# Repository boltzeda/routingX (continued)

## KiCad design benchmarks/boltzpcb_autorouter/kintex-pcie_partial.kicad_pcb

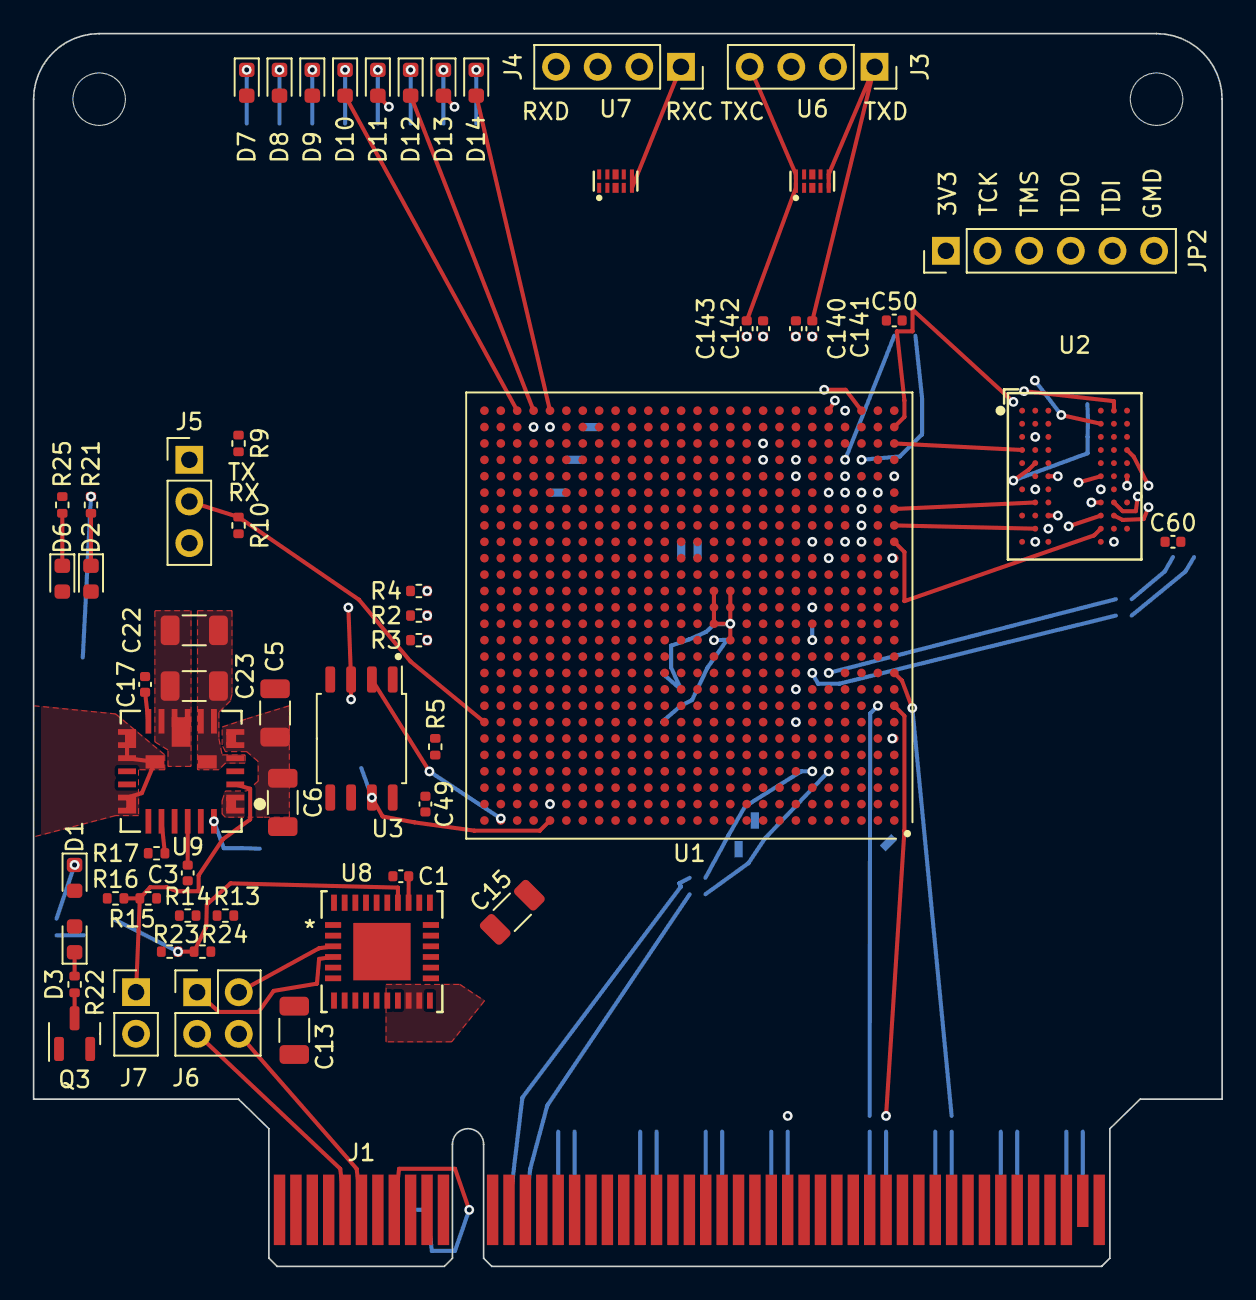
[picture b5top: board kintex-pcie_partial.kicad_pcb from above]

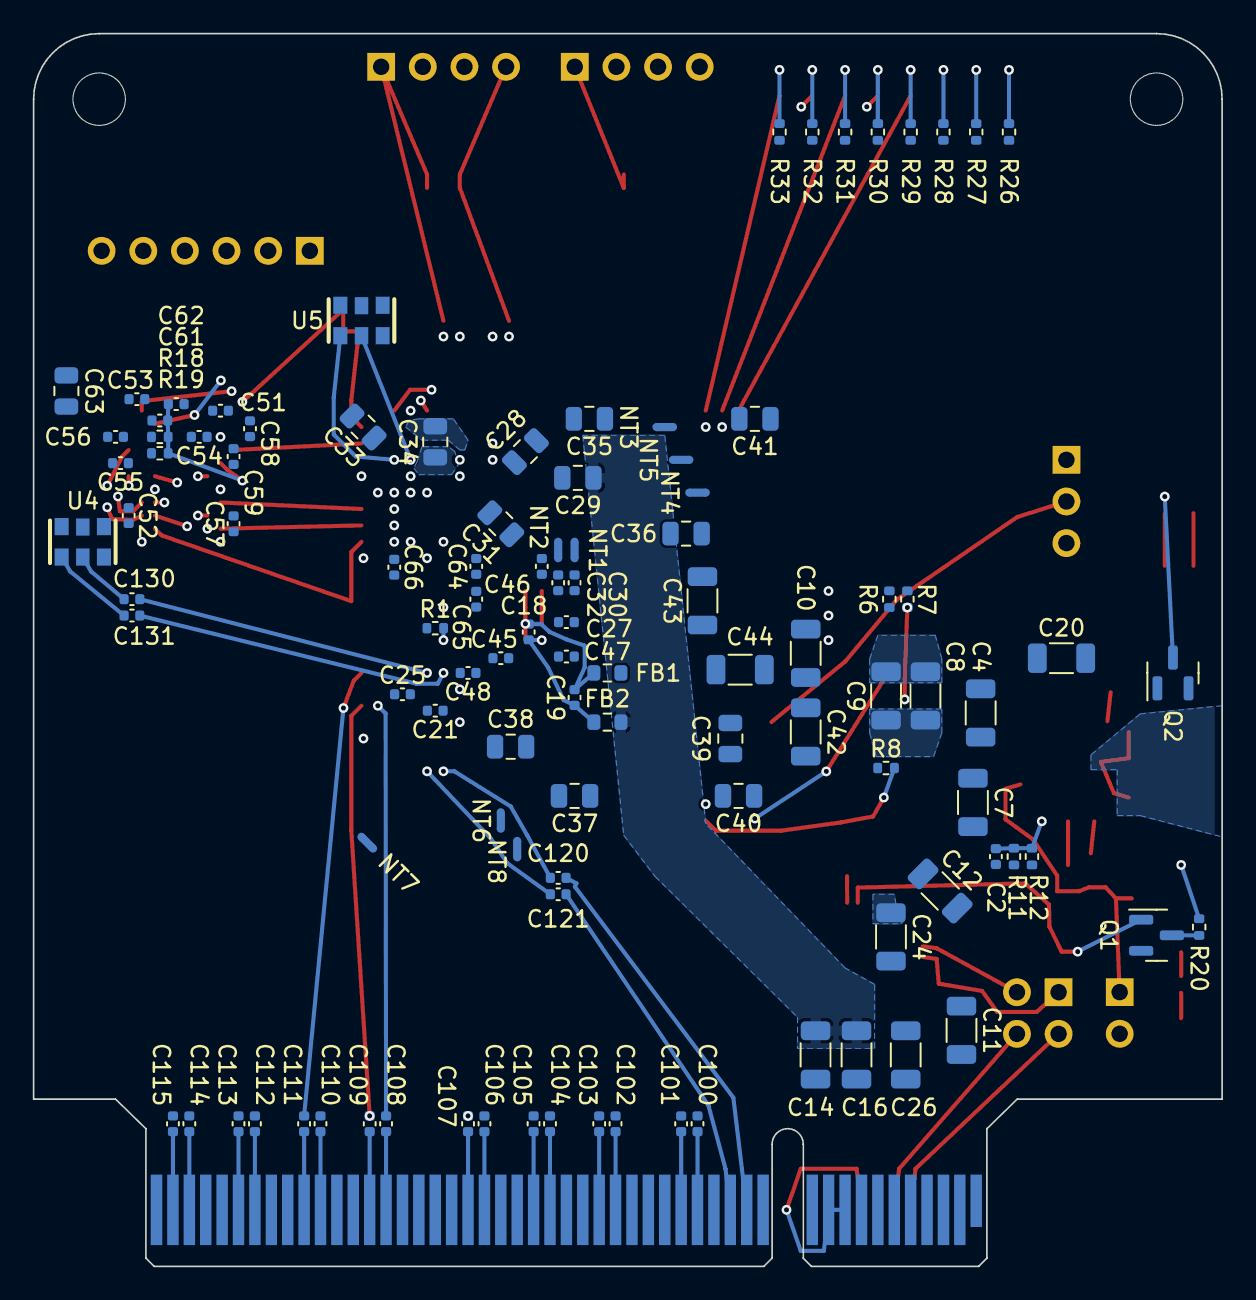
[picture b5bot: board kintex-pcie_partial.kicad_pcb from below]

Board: 8 copper layers, 72.5 x 75.2 mm, 166 parts (105 on the bottom side), 178 nets.

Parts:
C1, C17, C19: 1uF; C_0402_1005Metric
C2, C3: 4.7nF; C_0402_1005Metric
C4, C5, C6, C7, C8, C9, C10, C11, C12, C13, C14, C15, C16, C20, C22, C23, C24, C26: 22uF; C_1206_3216Metric
C18, C49, C50, C51, C52, C53, C54, C55, C56, C57, C58, C59, C60, C61, C62, C100, C101, C102, C103, C104, C105, C106, C107, C108, C109, C110, C111, C112, C113, C114, C115, C120, C121, C130, C131, C140, C141, C142, C143: 100nF; C_0402_1005Metric
C21, C25, C27, C30, C32, C45, C46, C47, C48, C64, C65, C66: 4.7uF; C_0402_1005Metric
C28, C29, C31, C33, C34, C35, C36, C37, C38, C39, C40, C41, C63: 47uF; C_0805_2012Metric
C42, C43, C44: 100uF; C_1206_3216Metric
D1, D2, D3, D6: GLED; LED_0603_1608Metric
D7, D8, D9, D10, D11, D12, D13, D14: RLED; LED_0603_1608Metric
FB1, FB2: 600R@100MHz; R_0603_1608Metric
H1, H2: MountingHole; MountingHole_3.2mm_M3
J1: Bus_PCI_Express_x8; BUS_PCIexpress_x8
J3: B2B_TX; PinSocket_1x04_P2.54mm_Vertical
J4: B2B_RX; PinSocket_1x04_P2.54mm_Vertical
J5: UART; PinHeader_1x03_P2.54mm_Vertical
J6: I2C_LINK; PinHeader_2x02_P2.54mm_Vertical
J7: 1V_EN; PinHeader_1x02_P2.54mm_Vertical
JP2: JTAG; PinHeader_1x06_P2.54mm_Vertical
NT1, NT2, NT3, NT4, NT5, NT6, NT7, NT8: NetTie_2; NetTie-2_SMD_Pad0.5mm
Q1, Q2, Q3: BSS138; SOT-23
R1: 100R; R_0402_1005Metric
R2, R3, R4, R5, R6, R7, R8, R9, R10, R20, R21, R22, R25, R26, R27, R28, R29, R30, R31, R32, R33: 4K7; R_0402_1005Metric
R11, R18, R19: 2K; R_0402_1005Metric
R12, R14, R16, R24: 3K; R_0402_1005Metric
R13, R15, R17, R23: 15K; R_0402_1005Metric
U1: XC7K160T-FFG676; Xilinx_FFG676
U2: MT47H64M8SH; FBGA-60_L10.0-W8.0-P0.80-TL_MICRON_MT47H64M8SH
U3: W25Q128JVS; SOIC-8_5.23x5.23mm_P1.27mm
U4, U5: OB3225125MLDB6SI-00; OSC-SMD_6P-L3.2-W2.5-BL_SG3225EAN
U6, U7: TPD4E02B04DQAR; USON-10_L2.5-W1.0-P0.50-BL
U8: MPM54304GMN-0000; LGA7x7x2_MNP
U9: MPM3683GQN-7-P; MPM3683GQN-7

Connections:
+1V0: C4.1, C5.1, C6.1, C7.1, C8.1, C9.1, C10.1, C27.1, C30.1, C32.1, C42.1, C43.1, C44.1, C45.1, C46.1, C47.1, C48.1, NT2.2, U1.J9 (VCCINT), U1.K8 (VCCINT), U1.K10 (VCCINT), U1.K12 (VCCINT), U1.K14 (VCCINT), U1.L9 (VCCINT), U1.L13 (VCCINT), U1.L15 (VCCINT), U1.M8 (VCCINT), U1.M14 (VCCINT), U1.N9 (VCCINT), U1.N13 (VCCBRAM), U1.N15 (VCCINT), U1.P14 (VCCINT), U1.R13 (VCCBRAM), U1.R15 (VCCINT), U1.T12 (VCCBRAM), U1.T14 (VCCINT), U1.U13 (VCCBRAM), U1.U15 (VCCINT), U9.1 (VOUT), U9.6 (VOUT)
+1V8: C14.1, C16.1, C28.1, C29.1, C31.1, C33.1, C34.1, C35.1, C50.1, C51.1, C52.1, C53.1, C54.1, C55.1, C56.1, C57.1, C58.1, C59.1, C60.1, C62.2, C63.1, C64.1, C65.1, C66.1, FB2.2, NT3.2, R18.1, U1.AA1 (VCCO_34), U1.AA11 (VCCO_33), U1.AB8 (VCCO_33), U1.AB18 (VCCO_32), U1.AC5 (VCCO_34), U1.AC15 (VCCO_32), U1.AD2 (VCCO_34), U1.AD12 (VCCO_33), U1.AE9 (VCCO_33), U1.AE19 (VCCO_32), U1.AF6 (VCCO_34), U1.AF16 (VCCO_32), U1.L11 (VCCAUX), U1.M10 (VCCAUX), U1.N6 (MGTVCCAUX), U1.P8 (VCCAUX_IO_G0), U1.P10 (VCCAUX), U1.R9 (VCCAUX_IO_G0), U1.T8 (VCCAUX_IO_G0), U1.T10 (VCCAUX), U1.U3 (VCCO_34), U1.U11 (VCCAUX), U1.V10 (VCCO_33), U1.W7 (VCCO_33), U1.W17 (VCCO_32), U1.Y4 (VCCO_34), U1.Y14 (VCCO_32), U2.A1 (VDD), U2.A9 (VDDQ), U2.C1 (VDDQ), U2.C3 (VDDQ), U2.C7 (VDDQ), U2.C9 (VDDQ), U2.E1 (VDDL), U2.E9 (VDD), U2.H9 (VDD), U2.L1 (VDD), U4.1 (OE), U4.6 (VDD), U5.1 (OE), U5.6 (VDD), U8.14 (VOUT1), U8.15 (VOUT1)
+3V3: C11.1, C13.1, C36.1, C37.1, C38.1, C39.1, C40.1, C41.1, C49.1, JP2.1, NT4.2, R2.2, R3.2, R4.2, R5.1, R6.1, R7.1, R8.1, R9.1, R10.1, U1.A11 (VCCO_16), U1.A21 (VCCO_14), U1.AA21 (VCCO_12), U1.AC25 (VCCO_12), U1.AD22 (VCCO_12), U1.AF26 (VCCO_12), U1.B8 (VCCO_16), U1.B18 (VCCO_15), U1.C15 (VCCO_16), U1.C25 (VCCO_14), U1.D12 (VCCO_16), U1.D22 (VCCO_14), U1.E9 (VCCO_16), U1.E19 (VCCO_15), U1.F16 (VCCO_15), U1.F26 (VCCO_14), U1.G13 (VCCO_16), U1.G23 (VCCO_14), U1.H10 (VCCO_16), U1.H20 (VCCO_15), U1.J17 (VCCO_15), U1.K24 (VCCO_13), U1.L7 (VCCO_0), U1.L21 (VCCO_14), U1.M18 (VCCO_15), U1.N25 (VCCO_13), U1.P7 (CFGBVS_0), U1.P22 (VCCO_13), U1.R19 (VCCO_13), U1.T5 (M0_0), U1.T6 (VCCO_0), U1.T16 (VCCO_13), U1.T26 (VCCO_13), U1.U23 (VCCO_12), U1.V20 (VCCO_12), U1.Y24 (VCCO_12), U3.8 (VCC), U8.8 (VOUT2), U8.9 (VOUT2)
+12V: C20.1, C22.1, C23.1, C24.1, C26.1, D1.2 (A), D2.2 (A), D3.2 (A), D6.2 (A), J1.A2 (+12V), J1.A3 (+12V), J1.B1 (+12V), J1.B2 (+12V), J1.B3 (+12V), R13.2, R15.2, R23.2, U8.28 (VIN), U8.29 (VIN), U9.5 (VIN), U9.8 (VIN), U9.9 (VIN), U9.27 (VIN)
/1V_EN: J7.1, R15.1, R16.2, U9.3 (EN)
/1V_PG: Q2.1 (G), R13.1, R14.2, U8.19 (EN), U9.4 (PG)
/3V3 PCIE: J1.A9 (+3.3V), J1.A10 (+3.3V), J1.B8 (+3.3V)
/B2B_RXC_N: J4.1, U1.AC11 (IO_L13N_T2_MRCC_33), U7.5 (IO4), U7.6 (NC)
/B2B_RXC_P: J4.2, U1.AB11 (IO_L13P_T2_MRCC_33), U7.4 (IO3), U7.7 (NC)
/B2B_RXD_N: J4.3, U1.AD13 (IO_L17N_T2_33), U7.2 (IO2), U7.9 (NC)
/B2B_RXD_P: J4.4, U1.AC13 (IO_L17P_T2_33), U7.1 (IO1), U7.10 (NC)
/B2B_TXC_C_N: C142.1, U1.AD9 (IO_L12N_T1_MRCC_33)
/B2B_TXC_C_P: C143.1, U1.AC9 (IO_L12P_T1_MRCC_33)
/B2B_TXC_N: C142.2, J3.3, U6.2 (IO2), U6.9 (NC)
/B2B_TXC_P: C143.2, J3.4, U6.1 (IO1), U6.10 (NC)
/B2B_TXD_C_N: C141.1, U1.AC7 (IO_L10N_T1_33)
/B2B_TXD_C_P: C140.1, U1.AB7 (IO_L10P_T1_33)
/B2B_TXD_N: C141.2, J3.1, U6.5 (IO4), U6.6 (NC)
/B2B_TXD_P: C140.2, J3.2, U6.4 (IO3), U6.7 (NC)
/DDR_125_N: U1.AC3 (IO_L14N_T2_SRCC_34), U5.4 (OUT+)
/DDR_125_P: U1.AC4 (IO_L14P_T2_SRCC_34), U5.5 (OUT-)
/DONE: R2.1, U1.J7 (DONE_0)
/FB: C2.2, R11.2, R12.1, U9.26 (VO_SENSE_P)
/GTX_125_C_N: C130.1, U4.5 (OUT-)
/GTX_125_C_P: C131.1, U4.4 (OUT+)
/GTX_125_N: C130.2, U1.K5 (MGTREFCLK1N_115)
/GTX_125_P: C131.2, U1.K6 (MGTREFCLK1P_115)
/INIT: R3.1, U1.G7 (INIT_B_0)
/LED0: D7.2 (A), U1.AE25 (IO_L23N_T3_12)
/LED1: D8.2 (A), U1.AF25 (IO_L20N_T3_12)
/LED2: D9.2 (A), U1.AD24 (IO_L16N_T2_12)
/LED3: D10.2 (A), U1.AF24 (IO_L20P_T3_12)
/LED4: D11.2 (A), U1.AE23 (IO_L22P_T3_12)
/LED5: D12.2 (A), U1.AF23 (IO_L22N_T3_12)
/LED6: D13.2 (A), U1.AE22 (IO_L24P_T3_12)
/LED7: D14.2 (A), U1.AF22 (IO_L24N_T3_12)
/MGTAVCC: C12.1, C21.1, NT6.2, U1.C6 (MGTAVCC), U1.E6 (MGTAVCC), U1.G6 (MGTAVCC), U1.J6 (MGTAVCC), U1.L6 (MGTAVCC), U8.1 (VOUT3), U8.32 (VOUT3)
/MGTAVTT: C15.1, C25.1, NT7.2, R1.1, U1.B3 (MGTAVTT), U1.C2 (MGTAVTT), U1.D3 (MGTAVTT), U1.G2 (MGTAVTT), U1.H3 (MGTAVTT), U1.L2 (MGTAVTT), U1.M3 (MGTAVTT), U1.M5 (MGTAVTTRCAL_115), U8.22 (VOUT4), U8.23 (VOUT4)
/MPM_PG: Q1.1 (G), R23.1, R24.2, U8.26 (GPIO)
/MPM_SCK: J6.1, U8.4 (SCL)
/MPM_SDA: J6.2, U8.3 (SDA)
/PCIE_SCK: J1.B5 (SMCLK), J6.3
/PCIE_SDA: J1.B6 (SMDAT), J6.4
/PCIE_TX0_C_N: C101.1, J1.A17 (PERn0)
/PCIE_TX0_C_P: C100.1, J1.A16 (PERp0)
/PCIE_TX1_C_N: C103.1, J1.A22 (PERn1)
/PCIE_TX1_C_P: C102.1, J1.A21 (PERp1)
/PCIE_TX2_C_N: C105.1, J1.A26 (PERn2)
/PCIE_TX2_C_P: C104.1, J1.A25 (PERp2)
/PCIE_TX3_C_N: C107.1, J1.A30 (PERn3)
/PCIE_TX3_C_P: C106.1, J1.A29 (PERp3)
/PCIE_TX4_C_N: C109.1, J1.A36 (PERn4)
/PCIE_TX4_C_P: C108.1, J1.A35 (PERp4)
/PCIE_TX5_C_N: C111.1, J1.A40 (PERn5)
/PCIE_TX5_C_P: C110.1, J1.A39 (PERp5)
/PCIE_TX6_C_N: C113.1, J1.A44 (PERn6)
/PCIE_TX6_C_P: C112.1, J1.A43 (PERp6)
/PCIE_TX7_C_N: C115.1, J1.A48 (PERn7)
/PCIE_TX7_C_P: C114.1, J1.A47 (PERp7)
/PERST: J1.A11 (~PERST), J7.2, Q3.1 (G)
/PROGRAM: R4.1, U1.P6 (PROGRAM_B_0)
/REFCLK_C_N: C121.2, J1.A14 (REFCLK-)
/REFCLK_C_P: C120.2, J1.A13 (REFCLK+)
/SPI_CLK: U1.C8 (CCLK_0), U3.6 (CLK)
/SPI_CS: R6.2, U1.C23 (IO_L6P_T0_FCS_B_14), U3.1 (~CS)
/SPI_D0: U1.B24 (IO_L1P_T0_D00_MOSI_14), U3.5 (DI(IO0))
/SPI_D1: U1.A25 (IO_L1N_T0_D01_DIN_14), U3.2 (DO(IO1))
/SPI_D2: R7.2, U1.B22 (IO_L2P_T0_D02_14), U3.3 (IO2)
/SPI_D3: R8.2, U1.A22 (IO_L2N_T0_D03_14), U3.7 (IO3)
/SW: U9.14 (SW), U9.16 (SW), U9.19 (SW), U9.28 (SW)
/TCK: JP2.2, U1.L8 (TCK_0)
/TDI: JP2.5, U1.R6 (TDI_0)
/TDO: JP2.4, U1.R7 (TDO_0)
/TMS: JP2.3, U1.N8 (TMS_0)
/UART_RX: J5.2, R10.2, U1.G26 (IO_L16N_T2_A15_D31_14)
/UART_TX: J5.1, R9.2, U1.H26 (IO_L18N_T2_A11_D27_14)
/VSENSE_N: NT1.2, R12.2, U9.25 (VO_SENSE_N)
/VSENSE_P: C2.1, NT2.1, R11.1
DDR_A0: U1.AA5 (IO_L15P_T2_DQS_34), U2.H8 (A0)
DDR_A1: U1.AC2 (IO_L11N_T1_SRCC_34), U2.H3 (A1)
DDR_A2: U1.W3 (IO_L4N_T0_34), U2.H7 (A2)
DDR_A3: U1.Y2 (IO_L7N_T1_34), U2.J2 (A3)
DDR_A4: U1.V4 (IO_L6P_T0_34), U2.J8 (A4)
DDR_A5: U1.AA3 (IO_L12P_T1_MRCC_34), U2.J3 (A5)
DDR_A6: U1.V6 (IO_L5N_T0_34), U2.J7 (A6)
DDR_A7: U1.W1 (IO_L10P_T1_34), U2.K2 (A7)
DDR_A8: U1.V2 (IO_L8P_T1_34), U2.K8 (A8)
DDR_A9: U1.Y3 (IO_L7P_T1_34), U2.K3 (A9)
DDR_A10: U1.Y1 (IO_L10N_T1_34), U2.H2 (A10)
DDR_A11: U1.V1 (IO_L8N_T1_34), U2.K7 (A11)
DDR_A12: U1.V3 (IO_L4P_T0_34), U2.L2 (A12)
DDR_A13: U1.U5 (IO_L1N_T0_34), U2.L8 (A13)
DDR_BA0: U1.AA2 (IO_L12N_T1_MRCC_34), U2.G2 (BA0)
DDR_BA1: U1.AC1 (IO_L9N_T1_DQS_34), U2.G3 (BA1)
DDR_CAS: U1.AA4 (IO_L13P_T2_MRCC_34), U2.G7 (~CAS)
DDR_CKE: U1.AB2 (IO_L11P_T1_SRCC_34), U2.F2 (CKE)
DDR_CK_N: U1.W5 (IO_L3N_T0_DQS_34), U2.F8 (~CK)
DDR_CK_P: U1.W6 (IO_L3P_T0_DQS_34), U2.E8 (CK)
DDR_DM: U1.AE3 (IO_L22P_T3_34), U2.B3 (DM)
DDR_DQ0: U1.AE5 (IO_L23N_T3_34), U2.C8 (DQ0)
DDR_DQ1: U1.AE1 (IO_L20N_T3_34), U2.C2 (DQ1)
DDR_DQ2: U1.AD3 (IO_L19N_T3_VREF_34), U2.D7 (DQ2)
DDR_DQ3: U1.AD4 (IO_L19P_T3_34), U2.D3 (DQ3)
DDR_DQ4: U1.AD1 (IO_L20P_T3_34), U2.D1 (DQ4)
DDR_DQ5: U1.AF3 (IO_L24P_T3_34), U2.D9 (DQ5)
DDR_DQ6: U1.AE2 (IO_L22N_T3_34), U2.B1 (DQ6)
DDR_DQ7: U1.AE6 (IO_L23P_T3_34), U2.B9 (DQ7)
DDR_DQS_N: U1.AF4 (IO_L21N_T3_DQS_34), U2.A8 (~DQS/NU)
DDR_DQS_P: U1.AF5 (IO_L21P_T3_DQS_34), U2.B7 (DQS)
DDR_ODT: U1.AB4 (IO_L13N_T2_MRCC_34), U2.F9 (ODT)
DDR_RAS: U1.U1 (IO_L2N_T0_34), U2.F7 (~RAS)
DDR_WE: U1.AB1 (IO_L9P_T1_DQS_34), U2.F3 (~WE)
GND: C1.2, C3.1, C4.2, C5.2, C6.2, C7.2, C8.2, C9.2, C10.2, C11.2, C12.2, C13.2, C14.2, C15.2, C16.2, C17.2, C20.2, C21.2, C22.2, C23.2, C24.2, C25.2, C26.2, C27.2, C28.2, C29.2, C30.2, C31.2, C32.2, C33.2, C34.2, C35.2, C36.2, C37.2, C38.2, C39.2, C40.2, C41.2, C42.2, C43.2, C44.2, C45.2, C46.2, C47.2, C48.2, C49.2, C50.2, C51.2, C52.2, C53.2, C54.2, C55.2, C56.2, C57.2, C58.2, C59.2, C60.2, C61.2, C63.2, C64.2, C65.2, C66.2, FB1.2, J1.A4 (GND), J1.A12 (GND), J1.A15 (GND), J1.A18 (GND), J1.A20 (GND), J1.A23 (GND), J1.A24 (GND), J1.A27 (GND), J1.A28 (GND), J1.A31 (GND), J1.A34 (GND), J1.A37 (GND), J1.A38 (GND), J1.A41 (GND), J1.A42 (GND), J1.A45 (GND), J1.A46 (GND), J1.A49 (GND), J1.B4 (GND), J1.B7 (GND), J1.B13 (GND), J1.B16 (GND), J1.B18 (GND), J1.B21 (GND), J1.B22 (GND), J1.B25 (GND), J1.B26 (GND), J1.B29 (GND), J1.B32 (GND), J1.B35 (GND), J1.B36 (GND), J1.B39 (GND), J1.B40 (GND), J1.B43 (GND), J1.B44 (GND), J1.B47 (GND), J1.B49 (GND), J5.3, JP2.6, NT1.1, NT5.2, NT8.2, Q1.2 (S), Q2.2 (S), Q3.2 (S), R14.1, R16.1, R17.2, R19.2, R24.1, R25.2, R26.2, R27.2, R28.2, R29.2, R30.2, R31.2, R32.2, R33.2, U1.A1 (GND), U1.A2 (GND), U1.A5 (GND), U1.A6 (GND), U1.A7 (GND), U1.A16 (GND), U1.A26 (GND), U1.AA6 (GND), U1.AA16 (GND), U1.AA26 (GND), U1.AB3 (GND), U1.AB13 (GND), U1.AB23 (GND), U1.AC10 (GND), U1.AC20 (GND), U1.AD7 (GND), U1.AD17 (GND), U1.AE4 (GND), U1.AE14 (GND), U1.AE24 (GND), U1.AF1 (GND), U1.AF11 (GND), U1.AF21 (GND), U1.B4 (GND), U1.B7 (GND), U1.B13 (GND), U1.B23 (GND), U1.C1 (GND), U1.C5 (GND), U1.C7 (GND), U1.C10 (GND), U1.C20 (GND), U1.D4 (GND), U1.D7 (GND), U1.D17 (GND), U1.E1 (GND), U1.E2 (GND), U1.E5 (GND), U1.E7 (GND), U1.E8 (VCCBATT_0), U1.E14 (GND), U1.E24 (GND), U1.F3 (GND), U1.F4 (GND), U1.F7 (GND), U1.F11 (GND), U1.F21 (GND), U1.G1 (GND), U1.G5 (GND), U1.G8 (GND), U1.G18 (GND), U1.H4 (GND), U1.H7 (GND), U1.H15 (GND), U1.H25 (GND), U1.J1 (GND), U1.J2 (GND), U1.J5 (GND), U1.J12 (GND), U1.J22 (GND), U1.K3 (GND), U1.K4 (GND), U1.K7 (GND), U1.K9 (GND), U1.K11 (GND), U1.K13 (GND), U1.K19 (GND), U1.L1 (GND), U1.L5 (GND), U1.L10 (GND), U1.L12 (GND), U1.L14 (GND), U1.L16 (GND), U1.L26 (GND), U1.M4 (GND), U1.M7 (GND), U1.M9 (GND), U1.M13 (GND), U1.M15 (GND), U1.M23 (GND), U1.N1 (GND), U1.N2 (GND), U1.N5 (GND), U1.N7 (GND), U1.N10 (GND), U1.N14 (GND), U1.N20 (GND), U1.P3 (GND), U1.P4 (GND), U1.P5 (M2_0), U1.P9 (GND), U1.P13 (GND), U1.P15 (GND), U1.P17 (GND), U1.R1 (GND), U1.R2 (GND), U1.R5 (GND), U1.R8 (GND), U1.R10 (GND), U1.R14 (GND), U1.R24 (GND), U1.T1 (GND), U1.T2 (M1_0), U1.T3 (GND), U1.T4 (GND), U1.T9 (GND), U1.T11 (GND), U1.T13 (GND), U1.T15 (GND), U1.T21 (GND), U1.U8 (GND), U1.U10 (GND), U1.U12 (GND), U1.U14 (GND), U1.U18 (GND), U1.V5 (GND), U1.V15 (GND), U1.V25 (GND), U1.W2 (GND), U1.W12 (GND), U1.W22 (GND), U1.Y9 (GND), U1.Y19 (GND), U2.A3 (VSS), U2.A7 (VSSQ), U2.B2 (VSSQ), U2.B8 (VSSQ), U2.D2 (VSSQ), U2.D8 (VSSQ), U2.E3 (VSS), U2.E7 (VSSDL), U2.G8 (~CS), U2.J1 (VSS), U2.K9 (VSS), U3.4 (GND), U4.3 (GND), U5.3 (GND), U6.3 (GND), U6.8 (GND), U7.3 (GND), U7.8 (GND), U8.2 (GND), U8.5 (GND), U8.7 (GND), U8.10 (GND), U8.13 (GND), U8.16 (GND), U8.20 (GND), U8.21 (GND), U8.27 (GND), U8.33 (GND), U9.10 (PGND), U9.12 (PGND), U9.18 (AGND), U9.21 (AGND)
GNDA: C18.1, C19.2, FB1.1, U1.M11 (GNDADC_0), U1.N11 (VREFN_0), U1.N12 (VP_0), U1.P11 (VN_0), U1.P12 (VREFP_0), U1.R11 (DXN_0), U1.R12 (DXP_0)
unnamed: D1.1 (K), R20.1
unnamed: D2.1 (K), R21.1
unnamed: D3.1 (K), R22.1
unnamed: D6.1 (K), R25.1
unnamed: D7.1 (K), R26.1
unnamed: D8.1 (K), R27.1
unnamed: D9.1 (K), R28.1
unnamed: D10.1 (K), R29.1
unnamed: D11.1 (K), R30.1
unnamed: D12.1 (K), R31.1
unnamed: D13.1 (K), R32.1
unnamed: D14.1 (K), R33.1
unnamed: J1.A1 (~PRSNT1), J1.B48 (~PRSNT2)
unnamed: Q1.3 (D), R20.2
unnamed: Q2.3 (D), R21.2
unnamed: Q3.3 (D), R22.2
unnamed: R1.2, U1.M6 (MGTRREF_115)
unnamed: R5.2, U1.B25 (IO_L3P_T0_DQS_PUDC_B_14)
unnamed: C61.1, C62.1, R18.2, R19.1, U2.E2 (VREF)
unnamed: NT4.1, U8.6 (FB2)
unnamed: NT5.1, U8.17 (SGND1)
unnamed: NT3.1, U8.18 (FB1)
unnamed: NT7.1, U8.24 (FB4)
unnamed: C1.1, U8.25 (VCC)
unnamed: NT8.1, U8.30 (SGND2)
unnamed: NT6.1, U8.31 (FB3)
unnamed: C17.1, U9.13 (VCC)
unnamed: R17.1, U9.22 (CS)
unnamed: C3.2, U9.24 (TRK/REF)
PCIE_RX0_N: J1.B15 (PETn0), U1.B5 (MGTXRXN3_116)
PCIE_RX0_P: J1.B14 (PETp0), U1.B6 (MGTXRXP3_116)
PCIE_RX1_N: J1.B20 (PETn1), U1.C3 (MGTXRXN2_116)
PCIE_RX1_P: J1.B19 (PETp1), U1.C4 (MGTXRXP2_116)
PCIE_RX2_N: J1.B24 (PETn2), U1.E3 (MGTXRXN1_116)
PCIE_RX2_P: J1.B23 (PETp2), U1.E4 (MGTXRXP1_116)
PCIE_RX3_N: J1.B28 (PETn3), U1.G3 (MGTXRXN0_116)
PCIE_RX3_P: J1.B27 (PETp3), U1.G4 (MGTXRXP0_116)
PCIE_RX4_N: J1.B34 (PETn4), U1.J3 (MGTXRXN3_115)
PCIE_RX4_P: J1.B33 (PETp4), U1.J4 (MGTXRXP3_115)
PCIE_RX5_N: J1.B38 (PETn5), U1.L3 (MGTXRXN2_115)
PCIE_RX5_P: J1.B37 (PETp5), U1.L4 (MGTXRXP2_115)
PCIE_RX6_N: J1.B42 (PETn6), U1.N3 (MGTXRXN1_115)
PCIE_RX6_P: J1.B41 (PETp6), U1.N4 (MGTXRXP1_115)
PCIE_RX7_N: J1.B46 (PETn7), U1.R3 (MGTXRXN0_115)
PCIE_RX7_P: J1.B45 (PETp7), U1.R4 (MGTXRXP0_115)
PCIE_TX0_N: C101.2, U1.A3 (MGTXTXN3_116)
PCIE_TX0_P: C100.2, U1.A4 (MGTXTXP3_116)
PCIE_TX1_N: C103.2, U1.B1 (MGTXTXN2_116)
PCIE_TX1_P: C102.2, U1.B2 (MGTXTXP2_116)
PCIE_TX2_N: C105.2, U1.D1 (MGTXTXN1_116)
PCIE_TX2_P: C104.2, U1.D2 (MGTXTXP1_116)
PCIE_TX3_N: C107.2, U1.F1 (MGTXTXN0_116)
PCIE_TX3_P: C106.2, U1.F2 (MGTXTXP0_116)
PCIE_TX4_N: C109.2, U1.H1 (MGTXTXN3_115)
PCIE_TX4_P: C108.2, U1.H2 (MGTXTXP3_115)
PCIE_TX5_N: C111.2, U1.K1 (MGTXTXN2_115)
PCIE_TX5_P: C110.2, U1.K2 (MGTXTXP2_115)
PCIE_TX6_N: C113.2, U1.M1 (MGTXTXN1_115)
PCIE_TX6_P: C112.2, U1.M2 (MGTXTXP1_115)
PCIE_TX7_N: C115.2, U1.P1 (MGTXTXN0_115)
PCIE_TX7_P: C114.2, U1.P2 (MGTXTXP0_115)
REFCLK_N: C121.1, U1.D5 (MGTREFCLK0N_116)
REFCLK_P: C120.1, U1.D6 (MGTREFCLK0P_116)
VDDA: C18.2, C19.1, FB2.1, U1.M12 (VCCADC_0)

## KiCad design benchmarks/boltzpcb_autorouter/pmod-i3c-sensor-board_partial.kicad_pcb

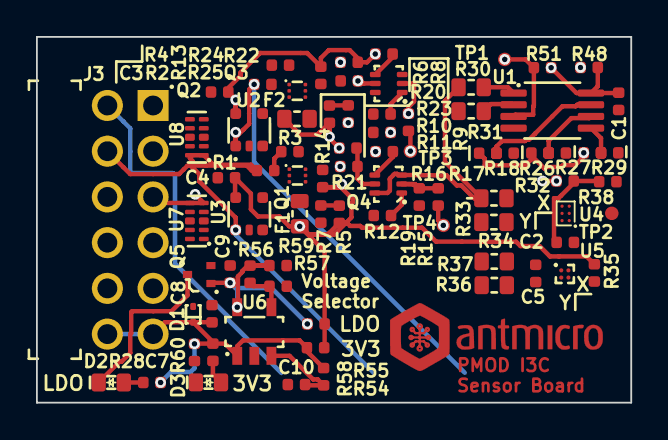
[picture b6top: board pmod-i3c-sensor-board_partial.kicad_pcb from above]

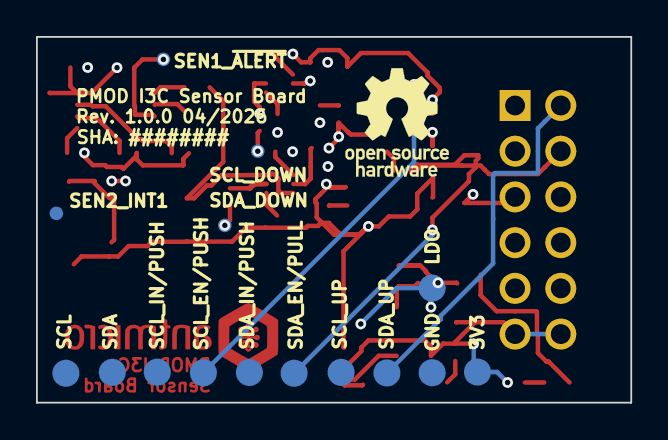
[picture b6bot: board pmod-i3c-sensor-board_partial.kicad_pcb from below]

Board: 4 copper layers, 33.0 x 20.3 mm, 90 parts (11 on the bottom side), 48 nets.

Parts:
C1, C2, C3, C4, C7, C10: C_100n_0402; C_0402_1005Metric
C5: C_2u2_0402; C_0402_1005Metric
C8, C9: C_1u_0402; C_0402_1005Metric
D1: ESD9X5.0ST5G; SOD-923
D2, D3: LED_G_0603_LTST-C190GKT; LED_0603_1608Metric_G
F1, F2: F_20mA_0603; F_0603_1608Metric
J3: PinHeader_2x6_P2.54mm_Drill1.1mm_Horizontal
Q1, Q2: DMC31D5UDJ; SOT-963
Q3, Q4: DMC2400UV-7; SOT-563
Q5: DMG1012T-7; SOT-523
R1, R2, R7, R8, R9, R15, R16, R17, R18, R21, R25, R26, R27, R29, R32, R35, R38, R48, R54, R55, R58: R_0R_0402; R_0402_1005Metric
R3, R4, R5, R6, R10, R13, R14, R19, R20, R24, R51: R_10k_0402; R_0402_1005Metric
R11, R12, R22, R23: R_2k_0402; R_0402_1005Metric
R28, R60: R_200R_0402; R_0402_1005Metric
R30, R31, R33, R34, R36, R37: R_0R_0603; R_0603_1608Metric
R56: R_41k2_0402; R_0402_1005Metric
R57: R_33k2_0402; R_0402_1005Metric
R59: R_100k_0402; R_0402_1005Metric
TP1, TP2, TP3, TP4: TP_0.75mm_SMD; TP_SMD_0.75mm
TP5, TP6, TP7, TP8, TP9, TP10, TP11, TP12, TP13, TP14, TP15: TP_1.5mm_SMD; TP_SMD_1.5mm
U1: P3T1755DP/Q900Z; TSSOP-8_3x3mm_P0.65mm
U2, U3: SN74LVC1G240_SC70; SOT-353
U4: BMA580; Bosch_WLCSP-6_0.84x1.18mm
U5: MMC5603NJ; WLP-4_0.82x0.82mm
U6: AP7366_SOT; SOT-23-5
U7, U8: TPD4E05U06QDQARQ1; USON-10_2.5x1mm_P0.5mm

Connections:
/LDO_OUTPUT: C9.2, Q5.1 (G), R55.1, R56.2, R59.2, TP14.1, U6.5 (OUT)
/PMOD_3V3: C7.2, C8.2, D1.1 (C), J3.11, J3.12, R28.2, R54.1, R58.2, R60.2, TP13.1, U6.1 (IN)
/SCL: J3.1, Q2.3 (D2), Q2.6 (D1), Q3.3 (D2), Q3.6 (D1), R13.1, R31.1, R34.1, R37.1, TP6.1, U2.4 (Y), U8.5, U8.6
/SCL_DOWN: R9.1, TP3.1
/SCL_EN/PULL: J3.5, R2.1, TP10.1, U2.1 (~OE), U7.5, U7.6
/SCL_IN/PUSH: J3.3, R8.2, TP8.1, U2.2 (A), U8.2, U8.9
/SCL_UP: J3.7, R25.2, TP12.1, U7.2, U7.9
/SDA: J3.8, Q1.3 (D2), Q1.6 (D1), Q4.3 (D2), Q4.6 (D1), R14.1, R30.1, R33.1, R36.1, TP5.1, U3.4 (Y), U7.1, U7.10
/SDA_DOWN: R15.1, TP4.1
/SDA_EN/PULL: J3.4, R1.1, TP9.1, U3.1 (~OE), U8.1, U8.10
/SDA_IN/PUSH: J3.6, R7.2, TP7.1, U3.2 (A), U7.4, U7.7
/SDA_UP: J3.2, R21.2, TP11.1, U8.4, U8.7
/SEN1_A0: R16.1, R17.2, U1.7 (A0)
/SEN1_A1: R18.1, R26.2, U1.6 (A1)
/SEN1_A2: R27.1, R29.2, U1.5 (A2)
/SEN1_VCC: C1.2, R16.2, R18.2, R27.2, R48.2, R51.2, U1.8 (VCC)
/SEN1_~ALERT: R51.1, TP1.1, U1.3 (~ALERT)
/SEN2_INT1: TP2.1, U4.2 (INT1)
/SEN2_INT2: R38.1, U4.3 (INT2)
/SEN2_VDD: C2.2, R32.2, R38.2, U4.6 (VDD)
/SEN3_VDD: C5.2, R35.2, U5.B1 (VDD)
GND: C1.1, C2.1, C3.1, C4.1, C5.1, C7.1, C8.1, C9.1, C10.1, D1.2 (A), D3.1 (C), J3.9, J3.10, Q1.1 (S1), Q2.1 (S1), Q5.2 (S), R3.1, R4.1, R10.1, R12.1, R17.1, R19.1, R23.1, R26.1, R29.1, R57.1, R59.1, TP15.1, U1.4 (GND), U2.3 (GND), U3.3 (GND), U4.1 (VSS), U5.A1 (VSA), U6.2 (GND), U7.3, U7.8, U8.3, U8.8
unnamed: D2.2 (A), R28.1
unnamed: D2.1 (C), Q5.3 (D)
unnamed: D3.2 (A), R60.1
unnamed: Q1.2 (G1), R1.2, R3.2
unnamed: Q1.5 (G2), R5.1, R7.1
unnamed: F1.1, Q1.4 (S2)
unnamed: Q2.2 (G1), R2.2, R4.2
unnamed: Q2.5 (G2), R6.1, R8.1
unnamed: F2.1, Q2.4 (S2)
unnamed: Q3.2 (G1), R9.2, R10.2
unnamed: Q3.5 (G2), R24.1, R25.1
unnamed: Q3.1 (S1), R23.2
unnamed: Q3.4 (S2), R22.1
unnamed: Q4.2 (G1), R15.2, R19.2
unnamed: Q4.5 (G2), R20.1, R21.1
unnamed: Q4.1 (S1), R12.2
unnamed: Q4.4 (S2), R11.1
unnamed: R31.2, U1.2 (SCL)
unnamed: R30.2, U1.1 (SDA)
unnamed: R34.2, U4.5 (SCL)
unnamed: R33.2, U4.4 (SDA)
unnamed: R37.2, U5.A2 (SCL)
unnamed: R36.2, U5.B2 (SDA)
unnamed: R56.1, R57.2, U6.4 (ADJ)
unnamed: C10.2, R58.1, U6.3 (EN)
VCC: C3.2, C4.2, F1.2, F2.2, R5.2, R6.2, R11.2, R13.2, R14.2, R20.2, R22.2, R24.2, R32.1, R35.1, R48.1, R54.2, R55.2, U2.5 (V_{CC}), U3.5 (V_{CC})
